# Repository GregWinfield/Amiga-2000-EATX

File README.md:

# Amiga 2000 EATX PCB

The [Scenario B+ engineering dashboard](dashboard/README.md) includes local preview instructions for inspecting the EATX board, comparing the two KiCad revisions and reviewing conversion evidence.

This is an open source Amiga 2000 PCB in the EATX form factor. EATX is an ATX variant that defines larger PCBs, measuring 12 x 13 inches (305 × 330 mm). These are referred to as Extended ATX, or, EATX (see [Enterprise Electronics Bay Specification](/DataSheets/SSI%20EEB%202011%201.0.1.pdf)). The length of Zorro II cards and the abundance of components on the Amiga 2000 makes EATX the best choice for this project.

There are one-to-one board replacement projects for the Amiga 2000, but none to change the layout to meet current form factor standards. In addition, the Amiga 2000 made use of connectors and custom parts that are no longer commercially manufactured. This often requires parts to be pulled from existing machines. As such, this project will make use of only actively supported components when possible.

In addition to a new board replacement option, I believe the ubiquitous EATX standard will bring additional interest to the Amiga as a hobbyist and retro-computing option. At the time or writting this, the Amiga operating system is still actively developed and supported. In addition, there is a substantial database of existing software and hardware add-on options and an active community.

Discord: https://discord.gg/NU7SPYfNFj

## Project Status

### Revision 3.1 is the current production board.

**Known Issues**: See Issues tab.

Revision 3.0 can be found [here](https://github.com/jasonsbeer/Amiga-2000-EATX/tree/Rev-3.0).  
Revision 2.2 can be found [here](https://github.com/jasonsbeer/Amiga-2000-EATX/tree/Rev-2.2).  
Revision 1.2.1 can be found [here](https://github.com/jasonsbeer/Amiga-2000-EATX/tree/Rev-1.2.1).  

If you are interested in a brief history of this project, check out the [Gallery page](/Gallery.md).

## User Guide and Considerations
Review [this information](userguide.md) to ensure a smooth and happy experience when assembling an Amiga 2000 EATX system. It will answer many questions and inform you as to the physical requirements of the Amiga 2000 EATX PCB, various Amiga plug in cards, etc.

## Ordering PCBs
See information [here](PCB.md). 

## BOM and Assembling the Amiga 2000 EATX PCB

See information [here](AssemblyNotes.md).

## Changes from the original Amiga 2000

The Amiga 2000 EATX is derived from the Commodore Amiga 2000 Rev 6.2 schematics. To my knowledge, all known Rev 6.x PCB updates are included in this project. 

### Video
The DB23 video connector has been removed in favor of the HD15 connector. One of the goals of this project is to avoid parts that are not commercially available. The D-Sub 23 connector is a prime example. They are not stocked at popular electronic supply houses. Thus, the change to the widely available HD15 connector. Analog red, green, blue, HSYNC or COMPSYNC (jumper selectable), and VSYNC are supplied using the VGA standard pin out configuration. Other external video port signals are not supplied. Any VGA cable can be used to supply the video signal to a VGA monitor or conversion box supporting the 15KHz standard. 

The internal video slot is complete with all signals.

The external composite video jack has been removed.

### Memory
The original 256Kx4 DRAMs have been replaced by a single SRAM. The Amiga 2000 EATX supports 1 or 2 MB of chip memory, depending on your Agnus version. See additional information in the [assembly notes](AssemblyNotes.md).

### Audio Output
The left/right RCA jacks of the Amiga have been replaced by a 3.5mm stereo audio jack.

### Disk Drive Support
Internally, any Amiga compatable double density disk drive or properly configured Gotek floppy emulator is supported. Up to two internal disk drives may be connected to the internal floppy connector. Up to two external disk drives may be connected via a user supplied adapter cable.

### ISA Slots
The number of 16 bit ISA slots has been reduced to three. This was done to provide additional space on the board. Support for ISA cards via a Bridgeboard is unchanged from the Amiga 2000.

### Serial Port
The internal (infernal) serial port has been removed. The external serial port is present with all signals.

### PCB Layout
For obvious reasons, it was necessary to move components relative to one another. Zorro slots occupy slot positions 1-5, overlapping with ISA slots in the first 3 positions. The video slot occupies the sixth slot position on the board.  The CPU slot occupies position 7. It is possible to have every slot position populated simultaneously.

### ATX Power
ATX 24-pin power supplies are supported with -5V being supplied on board via a voltage regulator. The original Amiga 2000 power supply is not supported.

### External Reset Switch
The computer can be reset via CTRL-Amiga-Amiga on an Amiga keyboard or via the reset switch found on EATX computer cases.

### Real Time Clock
There are two real time clock (RTC) options beginning with revision 2.x. You can install the original Amiga 2000 RTC, which is based on the MSM6242, or a simplified RTC based on the RTC-62423. The MSM6242 requires more components and will need to be trimmed to dial in the correct clock speed. The RTC-62423 has a built in crystal and does not need adjustment, but is less accurate over time. In the Amiga, the RTC is written and read by 4 address and 4 data lines. There are no direct "modern" replacements for the type of bus connected RTC used in the Amiga. As such, the RTC chip you choose is among the legacy IC's that must be obtained. 

### TICK
The TICK timing signal on the original Amiga 2000 was supplied by the power supply and is a 50 or 60Hz signal determined by the mains power in use. ATX power supplies do not supply a TICK or any AC signal. Starting with Revision 2.2, a TICK Header (J300) was added to support independently generated TICK signals in the event your desired configuration demands this. The factory default setting supplies a TICK signal from the Agnus _VSYNC signal, which is suitable for most configurations. See [TICK HEADER](/AssemblyNotes.md#tick-header-j300) for more details and considerations. All revisions 2.1 and lower use the Agnus _VSYNC signal.

## What has not changed?
### Most External Ports
The keyboard, joystick, mouse, parallel, and serial ports are all present and function as they did in the Amiga 2000. The parallel, serial, mouse, and joystick ports are stacked DB9 and DB25 connectors, respectively. The Amiga keyboard port remains a DIN5 connector.

### Zorro II Slots
There are no changes to the Zorro II slots.

### Kickstart ROM
For now, the Kickstart ROM remains the original 27C400. These are no longer made, but are easy to find. In addition, this allows the use of an original Commodore Kickstart mask ROM. Revision 1.2 added support for 1MB (27C800) and 2MB (27C160) EPROMs for custom Kickstart ROMs.

### Everything Else
If something is not specifically mentioned, you should expect it to be unchanged in function or component from the original Amiga 2000.

## Revision History

Rev 3.1 **CURRENT PRODUCTION REVISION**
1. Various fixes (see closed issues flagged for Revision 3.1)
2. Changed SRAM back to +5V part
3. Added copper pours to top and bottom layer
4. Updated to KiCAD 8.0

Rev 3.0
1. Various fixes (see closed issues flagged for Revision 3.0)
2. Changed SRAM to 5V tolerant 3.3V part (lack of availability of +5V part)
3. Removed almost all signal traces from power planes
4. Swapped position of U801 and U899 and brought related components to front of board
5. Updated to KiCAD 7.0

Rev. 2.2  
1. Added TICK header (J300)
2. Cleaned up some odd routing that went back to the early revisions of this project
3. Changed footprint of CN300 to support more part options

Rev 2.1
1. Changed footprint of U9000 to offer more part options
2. Added U207 to buffer VSYNC and HSYNC signals
3. Relocated Zorro termination components
4. Added additional component values to silk screen
5. Moved many traces to the external layers

Rev 2.0
1. Supports both Agnus 8372A and certain Agnus 8375 part numbers on the same board
2. Added external floppy drive header
3. Support for two real-time clock options
4. Cleaned up the schematics

Rev 1.2.1 (First Production Release)
1. Added some missing component values to the silk screen, where there was room
2. Moved VIDIOT over to make additional room for coprocessor cards

Rev 1.2
1. Fixed traces on the keyboard connector (error on the C= schematic)
2. Added missing _COPCFG trace
3. Deleted some extra traces that were not needed
4. Added HSYNC/COMPSYNC selection jumper
5. Cleaned up parts of the schematics
6. Widened U801 footprint (RTC62423 is wider than the standard SOIC package)
7. Added support for 1 and 2 MB Kickstart ROMs (512k still supported)
8. Added some space around the external ports...they were crowded

Rev 1.1
1. New ATX on/off circuit
2. Modified SRAM circuit
3. Added case fan header
4. Fixed U100 and other footprints
5. Moved some components
6. Cleaned up silk screen

Rev 1.0
1. Adjusted postion of slots and several other components
2. Moved ATX On/Off circuit to back of board

Rev 0 - Prototype board
   
## Acknowledgments
kr239 - for the Amiga 500 DRAM replacement project inspiration and LIV2 and texneus for the modifications used in this project

iansbremmer - Amiga IC KiCad footprints - https://github.com/iansbremner/ReAmiga-3000---KiCAD

texneus - ATX ON/OFF and AC TICK circuit

DarrenHD - Pics and measurements of the Amiga 3000 video slot bracket adapter - https://eab.abime.net/showthread.php?t=106928

Chucky - Amiga Diagrom...a priceless diagnostic tool - http://www.diagrom.com/

floppie209 - For testing the Rev 3.0 board.

Everyone that made the Amiga possible.

**Last Updated 02-JUN-2024**

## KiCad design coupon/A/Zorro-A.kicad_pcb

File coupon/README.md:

# Zorro II expansion termination coupons

Three separate KiCad 10 projects exercise nine adjacent Zorro data paths. Each project has its own schematic and routed four-layer board. Building three separate boards avoids branch-selection jumpers and unused termination stubs. The design files and fabrication archives are for review. [Assembly BOM](BOM.csv) · [Pin and length table](lanes.csv) · [Electrical acceptance plan](MEASUREMENT_PLAN.md)

| Coupon | Network under test | Slot-to-capacitor copper | Private RC copper | Files |
|---|---|---:|---:|---|
| A | Nine R3.1 0805 capacitors and nine R3.1 0805 resistors. Production lands and private traces. Slot escapes adjusted to the TE footprint. | 12.47–33.35 mm | 2.54–2.61 mm | [Project](A/Zorro-A.kicad_pro) · [Gerbers and drill](fabrication-review/Zorro-A-review.zip) |
| B | Nine radial 1 nF capacitors, each with a unique junction to a separate element of one 1 kΩ bussed SIP. Pin 1 goes to ground. | 9.87–15.37 mm | 18.50–24.93 mm | [Project](B/Zorro-B.kicad_pro) · [Gerbers and drill](fabrication-review/Zorro-B-review.zip) |
| C | Nine radial 1 nF capacitors and nine individual 1 kΩ compact axial resistors, each with its own return hole. | 9.87–15.37 mm | 12.42–16.92 mm | [Project](C/Zorro-C.kicad_pro) · [Gerbers and drill](fabrication-review/Zorro-C-review.zip) |

For a given signal, all three source-to-socket paths have identical drawn lengths. Across the nine lanes the range is 168.26–171.00 mm. T9/BD4 uses J1.18, J2.83 and the C9 private junction. A retains the C672/R605F1 private branch there. B routes that private node to RN1.10. The different B/C branch lengths let the fixture compare both package and practical routing effects. A matched-length package-only study would answer a different question. [Actual path lengths for each lane](lanes.csv)

## Assembly and fabrication review

- Open each project from this checkout. The common symbol library is one directory above the projects. A's local 0805 library captures Jason Beer's production lands. J2 uses the TE 5645235-3 solder socket with the card datum held fixed. The two rows are 4.85 mm apart. All 100 holes are 1.02 mm finished, with 1.53 mm outer lands and 1.80 mm inner lands. Twelve of the electrical tails also provide retention. Fabrication requires the supplier and sample checks. [Connector resolution](CONNECTOR_RESOLUTION.md) · [Manufacturing status and equipment](FABRICATION_READINESS.md)
- Each ZIP contains four Gerber copper layers, two mask layers, two silkscreen layers, Edge.Cuts, the Gerber job and metric Excellon drill. All drill features in these coupons are plated. The board centreline bounds are 223 × 149 mm with an L-shaped outline. Read the Gerber job and compare the submitted stack with the actual production build. Nominal order is F.Cu signal/GND, In1.Cu GND, In2.Cu external +5 V, B.Cu load/ground. Use 1.6 mm, green mask and white silk throughout. Confirm actual stack and impedance before comparing measurements.
- On each board J1 is the left header. J2 is the long socket. Facing the component side in PCB coordinates, C1 to C9 follow increasing Y in the branch bank. On A, resistor and capacitor rows lie alongside one another. On B, RN1 pin 1 is the return at the low-Y end, with pins 2–10 in lane order. On C the resistors form the outer row. CL1–CL9 are on the rear, alongside their socket contacts. Probe pads T1–T9 each have a ground pad just beside them. Use the KiCad F.Fab and B.Fab layers for exact reference placement. Use a passive termination card or the fixture load pads for the documented load sweep.
- KEMET's radial candidate has 2.54 mm lead pitch and a 3.81 × 2.54 mm maximum body plan. Check its formed leads in the 2.50 mm nominal footprint. Use the same measured capacitor lot for B and C. The 5.08 mm axial lead form and the shared SIP common impedance require physical verification. [KEMET specification](https://yageogroup.com/download/specsheet/C315C102J5G5TA) · [Vishay axial family](https://www.vishay.com/docs/28724/mrs16m25.pdf) · [Bourns SIP](https://bourns.com/docs/Product-Datasheets/4600x.pdf)

## Verification

KiCad 10.0.8 reported **zero ERC findings, zero DRC findings, zero unconnected pads and zero schematic parity differences** for each coupon. No rule exclusions were introduced. The independent check compares every schematic pin to its board pad, verifies all 27 lane paths and their private-node membership, and checks all 100 socket positions and their four-layer lands, and compares A's routes with R3.1 (0.100 mm allowance for the modified escape, 0.001 mm for each private branch). Run `python coupon/verify.py` with KiCad's Python interpreter and CLI available. These checks cover connectivity and drawn geometry. Bench testing and factory stack confirmation are open. [Check script](verify.py) · [Saved reports](checks) · [Test procedure](MEASUREMENT_PLAN.md)

The R3.1-derived slot, 0805 lands and A control traces retain the upstream project's attribution and repository licence. The historical scans and reconstructions are linked from the comparison report. [Upstream acknowledgement](../README.md) · [Repository licence](../LICENSE)

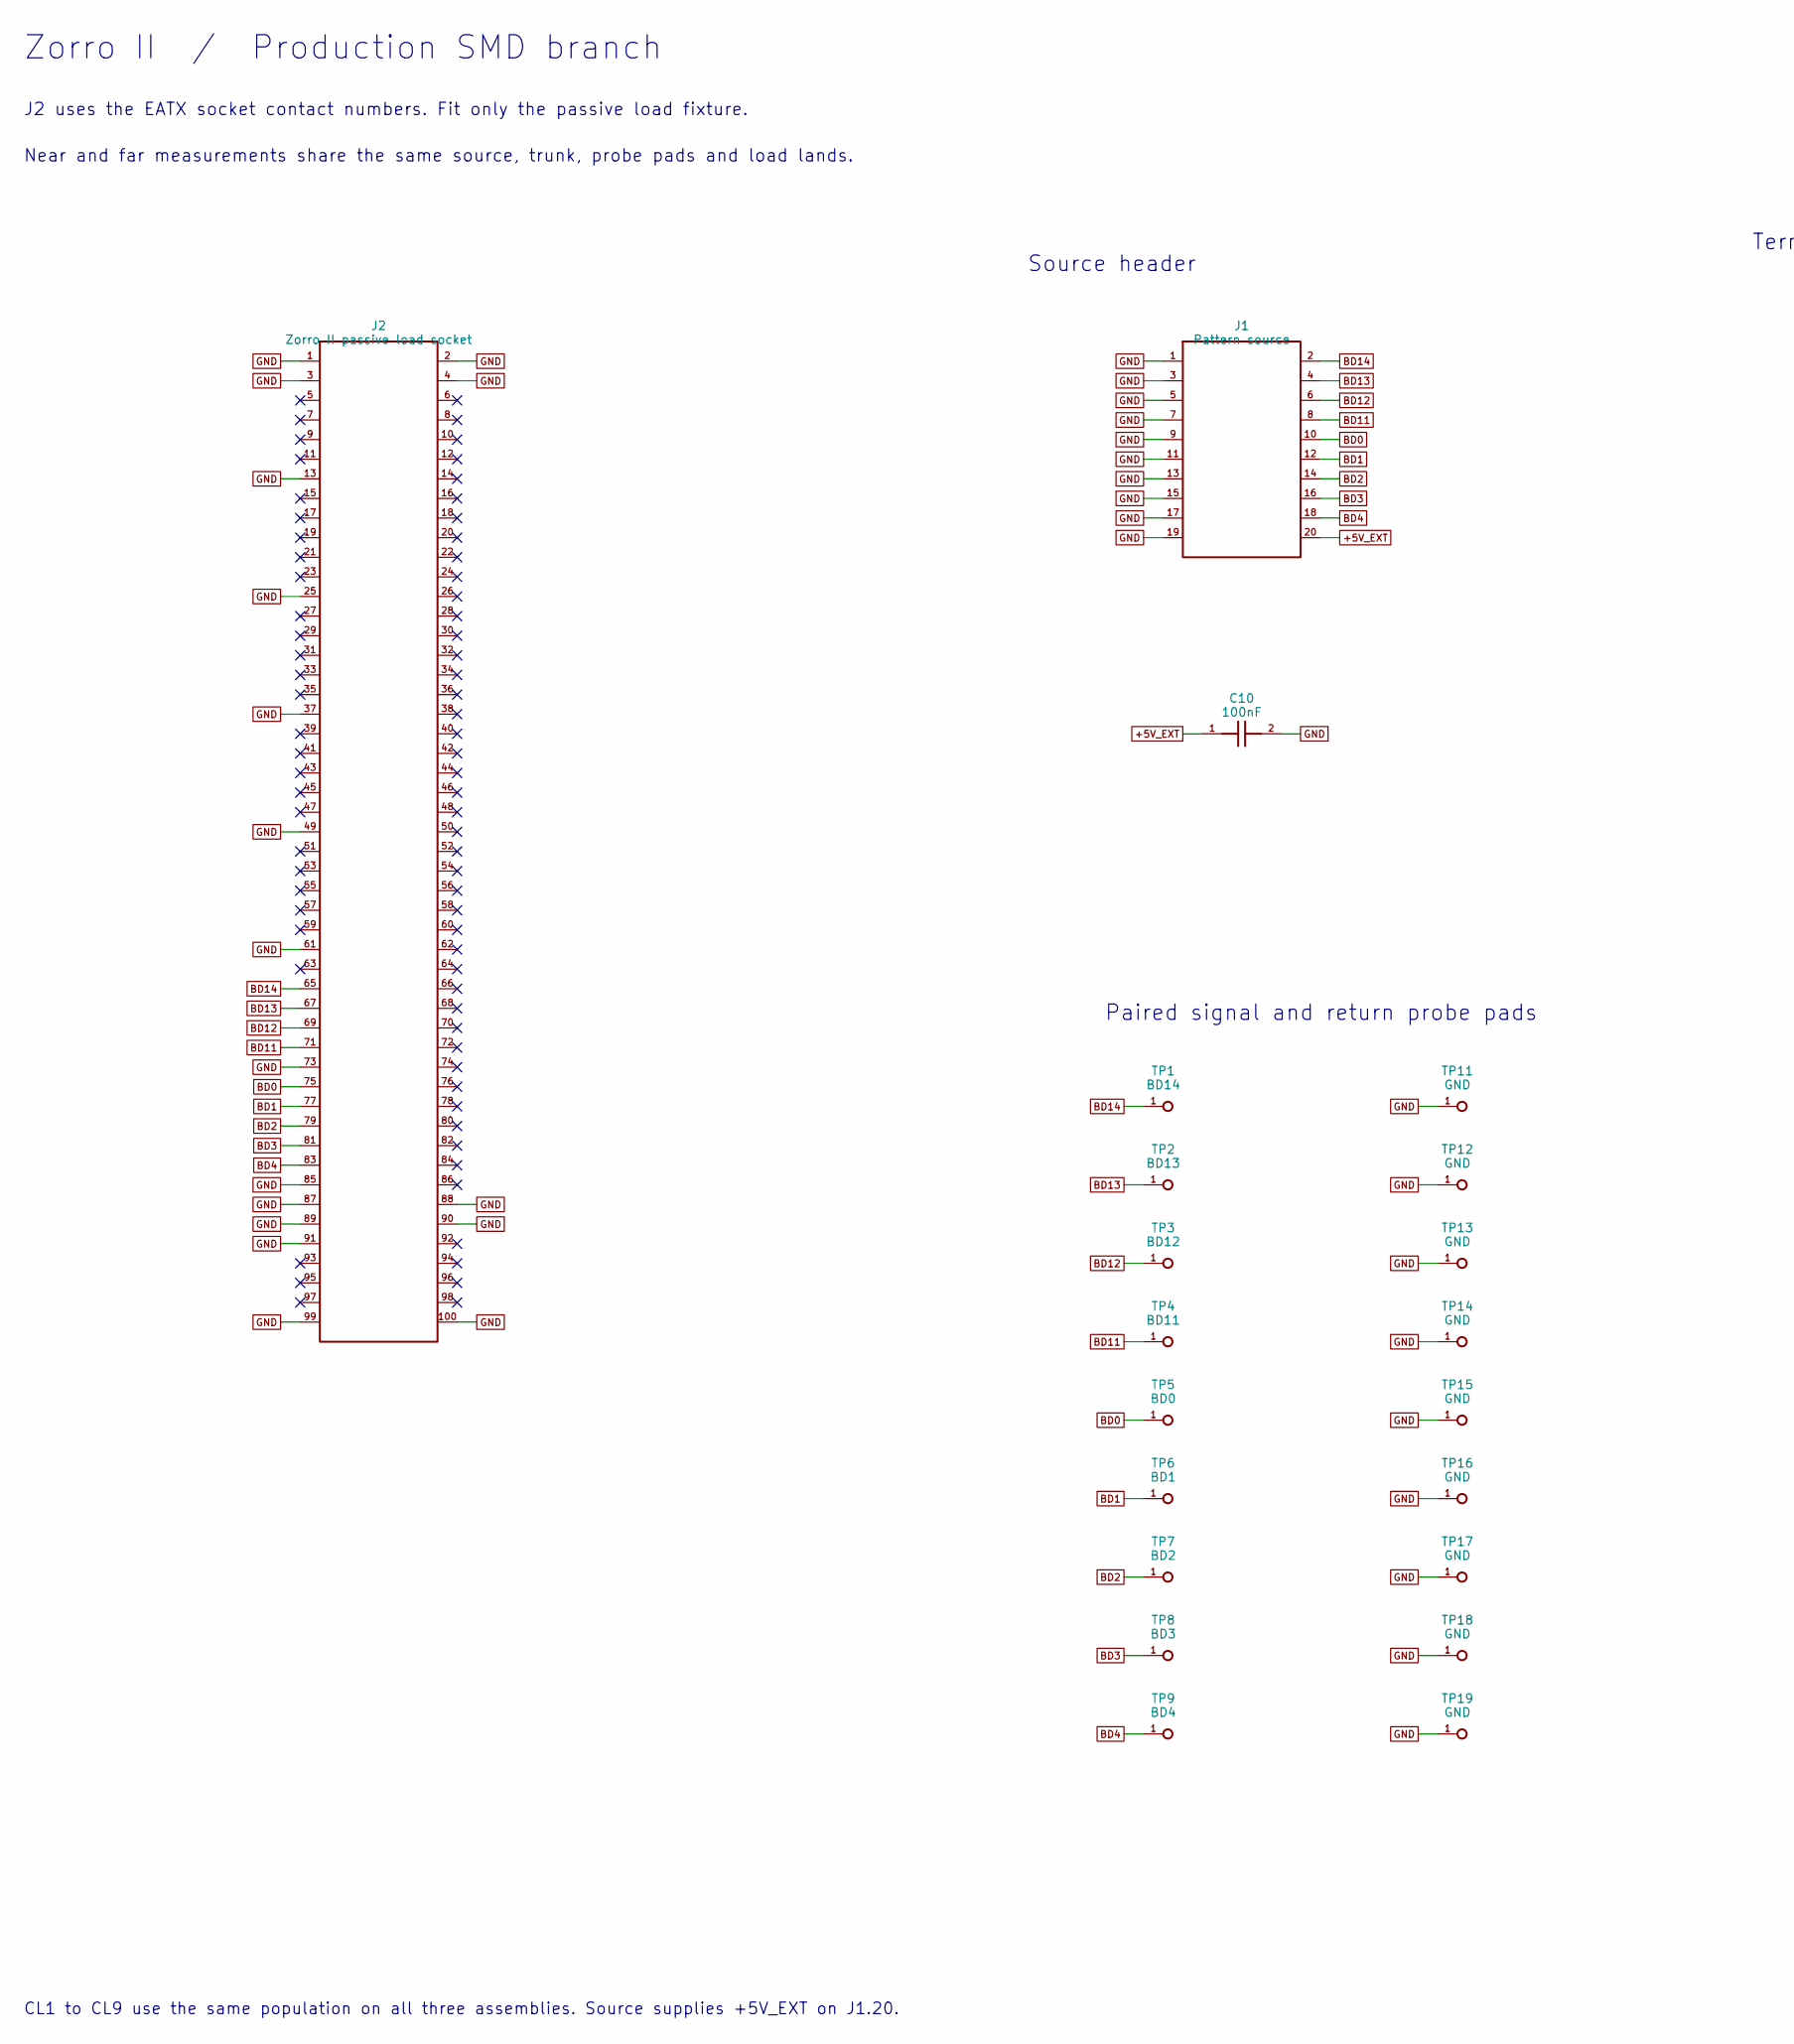
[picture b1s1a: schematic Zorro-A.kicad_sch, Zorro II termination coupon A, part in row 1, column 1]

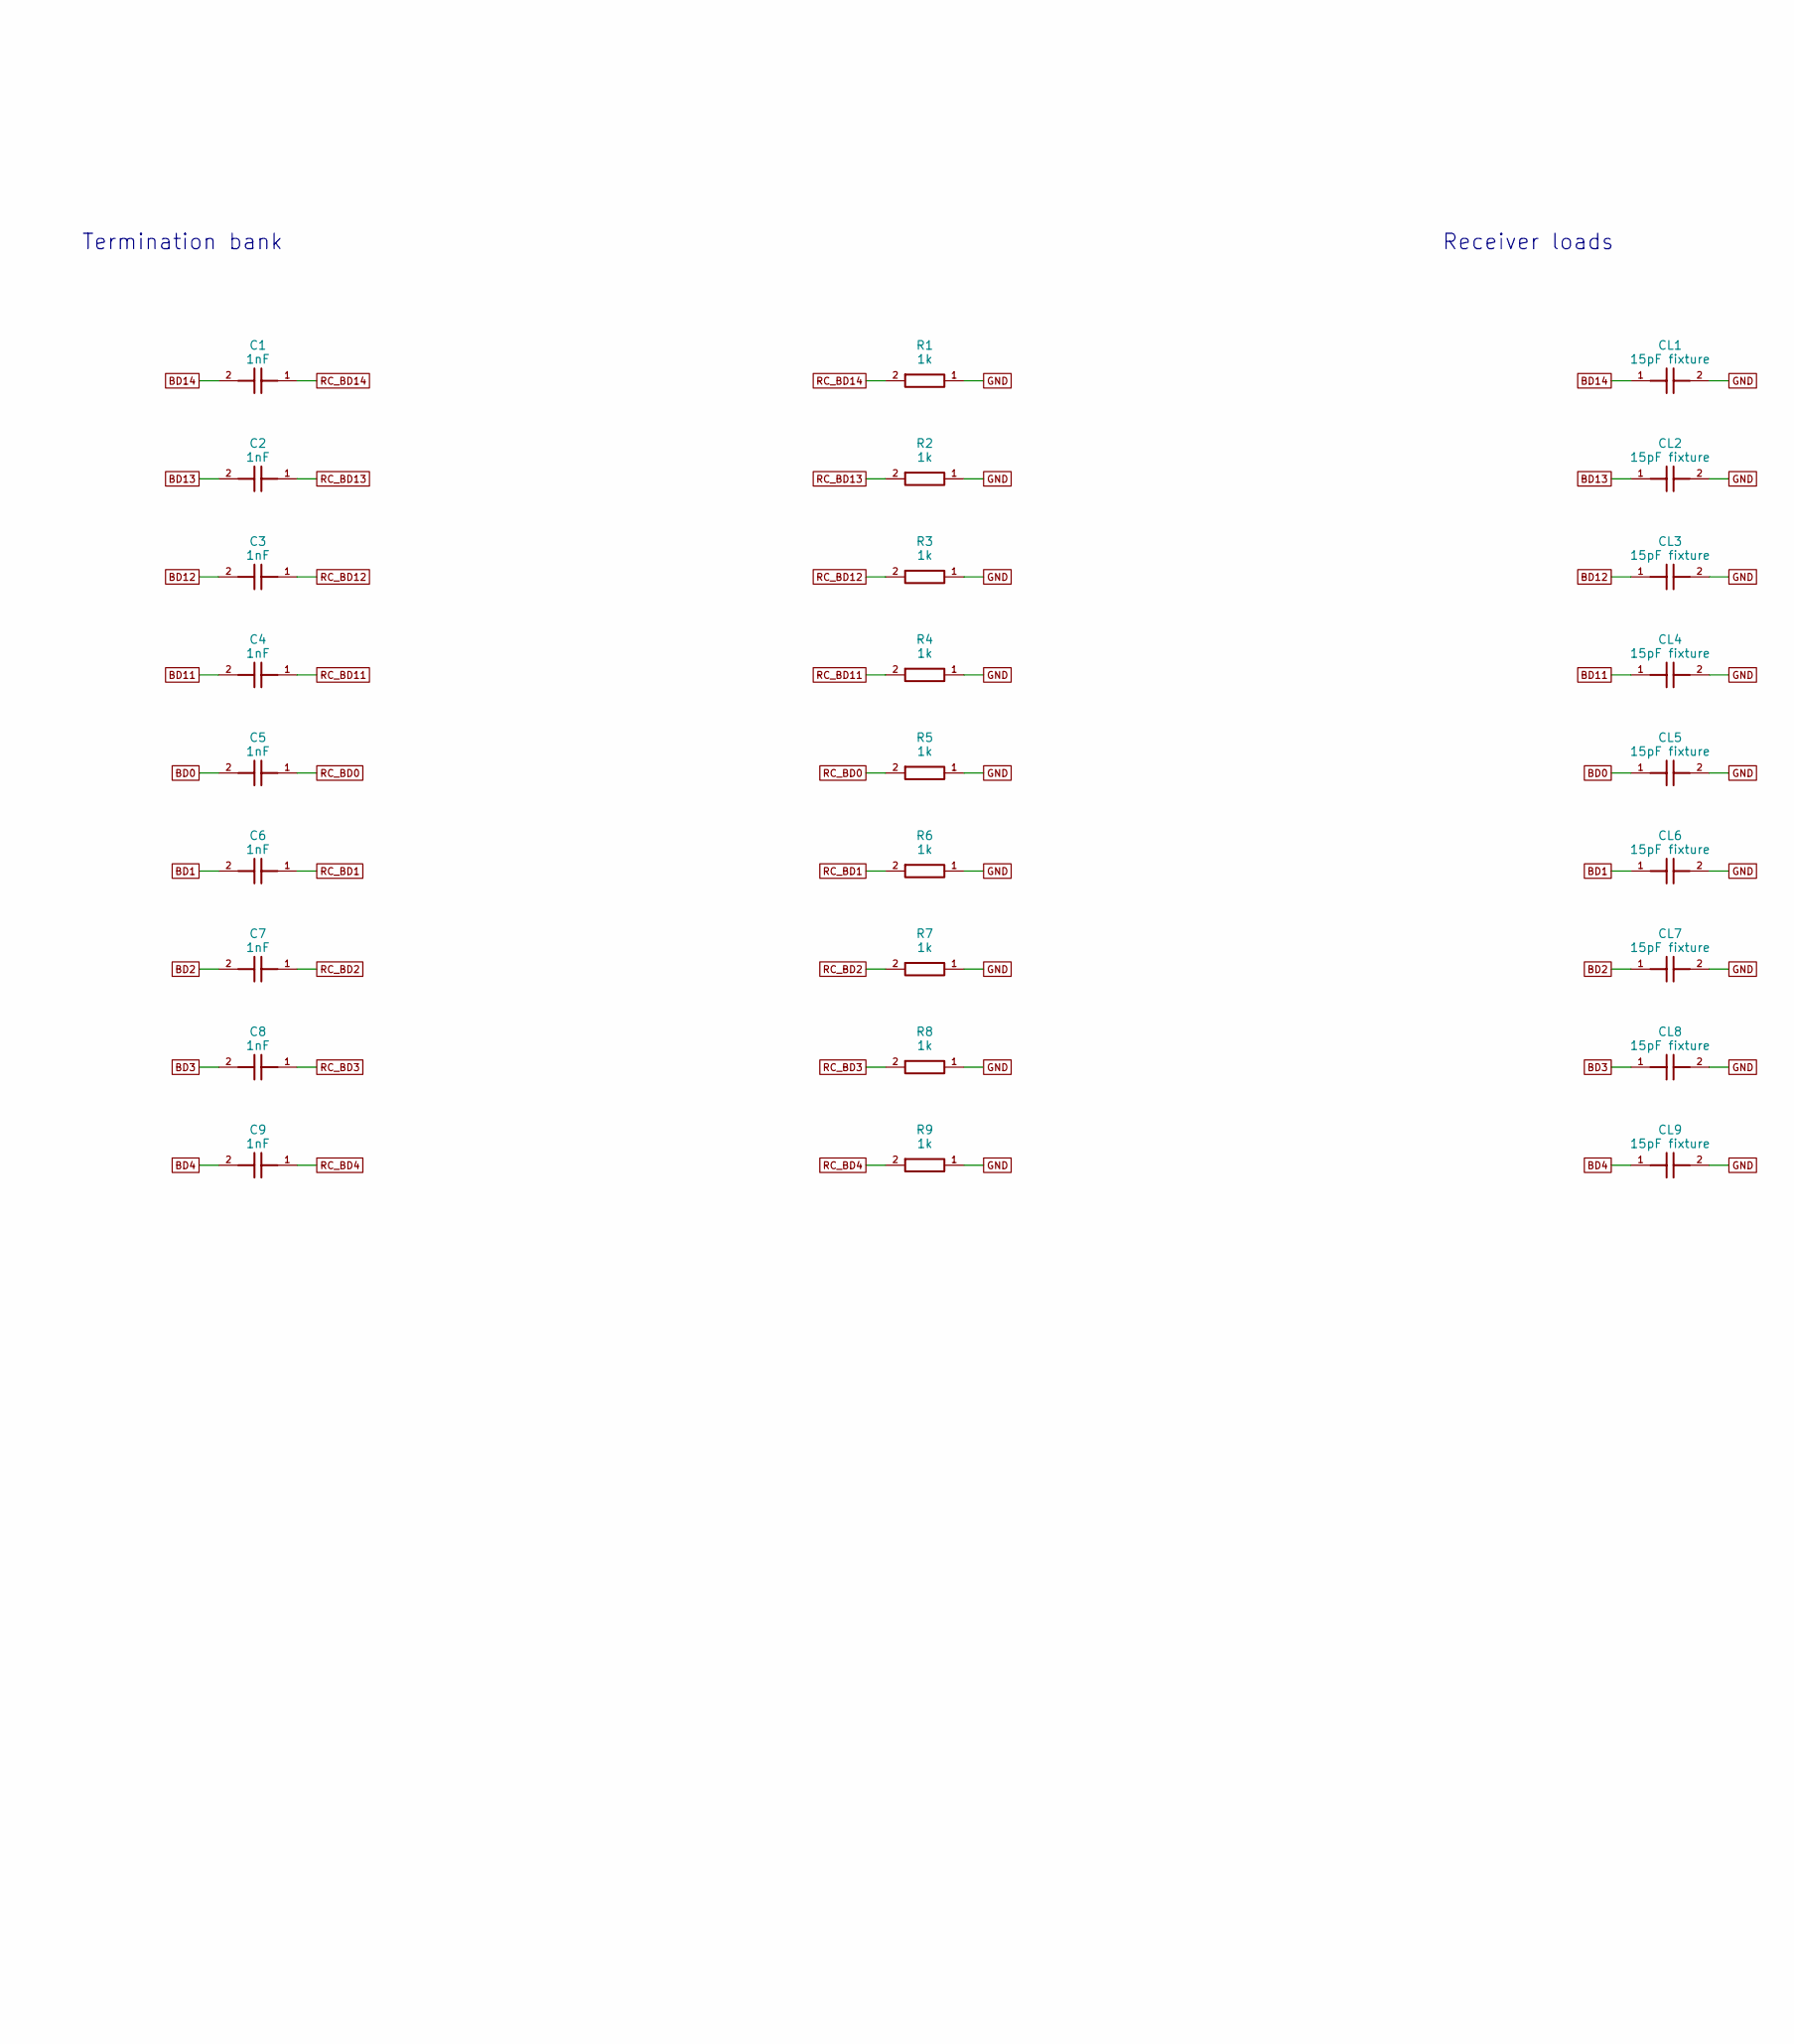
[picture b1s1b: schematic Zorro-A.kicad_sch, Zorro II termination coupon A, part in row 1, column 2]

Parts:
C1, C2, C3, C4, C5, C6, C7, C8, C9: 1nF; C_0805_2012Metric
C10: 100nF; C_0805_2012Metric
CL1, CL2, CL3, CL4, CL5, CL6, CL7, CL8, CL9: 15pF fixture; C_0805_2012Metric
J1: Pattern source; PinHeader_2x10_P2.54mm_Vertical
J2: Zorro II passive load socket; Zorro_5645235-3_coupon
R1, R2, R3, R4, R5, R6, R7, R8, R9: 1k; R_0805_2012Metric
TP1: BD14; TestPoint_Pad_D1.0mm
TP2: BD13; TestPoint_Pad_D1.0mm
TP3: BD12; TestPoint_Pad_D1.0mm
TP4: BD11; TestPoint_Pad_D1.0mm
TP5: BD0; TestPoint_Pad_D1.0mm
TP6: BD1; TestPoint_Pad_D1.0mm
TP7: BD2; TestPoint_Pad_D1.0mm
TP8: BD3; TestPoint_Pad_D1.0mm
TP9: BD4; TestPoint_Pad_D1.0mm
TP11, TP12, TP13, TP14, TP15, TP16, TP17, TP18, TP19: GND; TestPoint_Pad_D1.0mm

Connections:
+5V_EXT: C10.1, J1.20
BD0: C5.2, CL5.1, J1.10, J2.75, TP5.1
BD1: C6.2, CL6.1, J1.12, J2.77, TP6.1
BD2: C7.2, CL7.1, J1.14, J2.79, TP7.1
BD3: C8.2, CL8.1, J1.16, J2.81, TP8.1
BD4: C9.2, CL9.1, J1.18, J2.83, TP9.1
BD11: C4.2, CL4.1, J1.8, J2.71, TP4.1
BD12: C3.2, CL3.1, J1.6, J2.69, TP3.1
BD13: C2.2, CL2.1, J1.4, J2.67, TP2.1
BD14: C1.2, CL1.1, J1.2, J2.65, TP1.1
GND: C10.2, CL1.2, CL2.2, CL3.2, CL4.2, CL5.2, CL6.2, CL7.2, CL8.2, CL9.2, J1.1, J1.3, J1.5, J1.7, J1.9, J1.11, J1.13, J1.15, J1.17, J1.19, J2.1, J2.2, J2.3, J2.4, J2.13, J2.25, J2.37, J2.49, J2.61, J2.73, J2.85, J2.87, J2.88, J2.89, J2.90, J2.91, J2.99, J2.100, R1.1, R2.1, R3.1, R4.1, R5.1, R6.1, R7.1, R8.1, R9.1, TP11.1, TP12.1, TP13.1, TP14.1, TP15.1, TP16.1, TP17.1, TP18.1, TP19.1
RC_BD0: C5.1, R5.2
RC_BD1: C6.1, R6.2
RC_BD2: C7.1, R7.2
RC_BD3: C8.1, R8.2
RC_BD4: C9.1, R9.2
RC_BD11: C4.1, R4.2
RC_BD12: C3.1, R3.2
RC_BD13: C2.1, R2.2
RC_BD14: C1.1, R1.2

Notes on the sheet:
Zorro II / Production SMD branch
J2 uses the EATX socket contact numbers. Fit only the passive load fixture.
Near and far measurements share the same source, trunk, probe pads and load lands.
Termination bank
Receiver loads
Source header
Paired signal and return probe pads
CL1 to CL9 use the same population on all three assemblies. Source supplies +5V_EXT on J1.20.

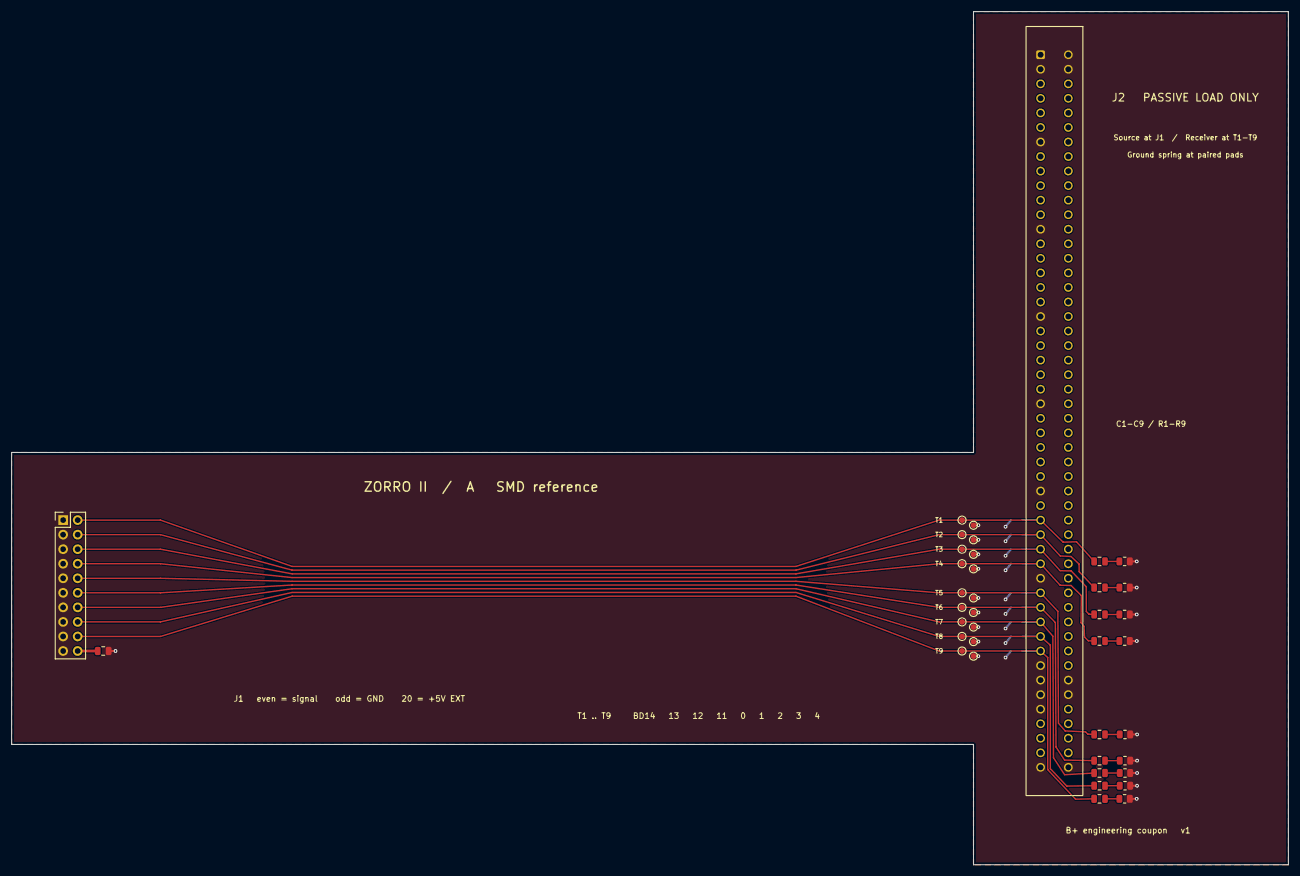
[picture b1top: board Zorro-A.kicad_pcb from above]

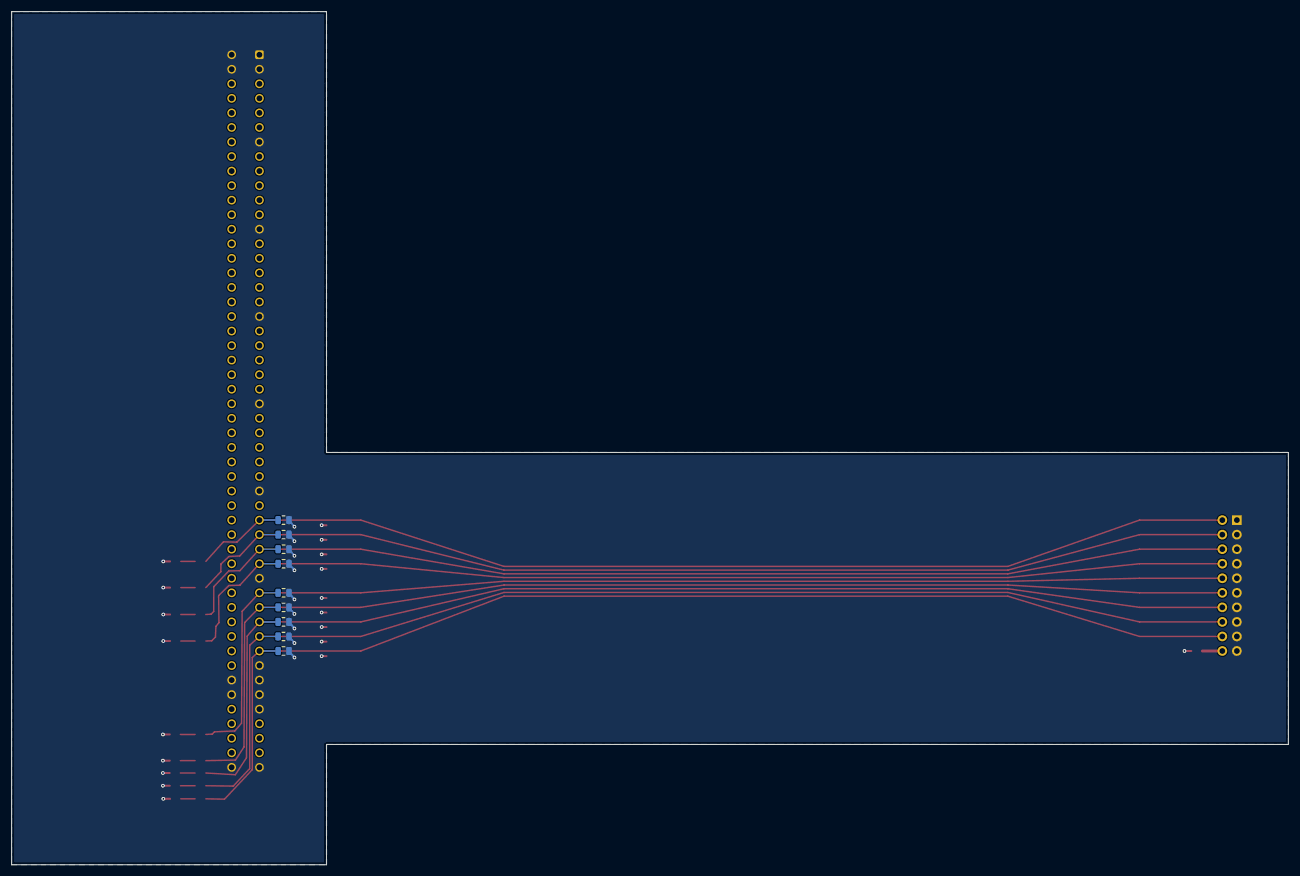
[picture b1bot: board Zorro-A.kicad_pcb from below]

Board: 4 copper layers, 223.0 x 149.0 mm, 48 parts (9 on the bottom side), 20 nets.
